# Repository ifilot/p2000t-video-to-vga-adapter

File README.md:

# P2000T video-to-VGA adapter

Hardware and firmware for converting the Philips P2000T RGBS output to
640×480 VGA using a Raspberry Pi Pico or Pico 2.

## Downloads

- [Latest Pico firmware](https://github.com/ifilot/p2000t-video-to-vga-adapter/releases/latest/download/p2000t-vid2vga-pico.uf2)
- [Latest Pico 2 firmware](https://github.com/ifilot/p2000t-video-to-vga-adapter/releases/latest/download/p2000t-vid2vga-pico2.uf2)
- [SAA5050 screen-test cartridge](https://github.com/ifilot/p2000t-video-to-vga-adapter/releases/latest/download/p2000t-screentest.bin)
- [Latest Windows capture viewer installer](https://github.com/ifilot/p2000t-video-to-vga-adapter/releases/latest/download/p2000t-vid2vga-capture-windows-setup.exe)
- [Latest portable Windows capture viewer](https://github.com/ifilot/p2000t-video-to-vga-adapter/releases/latest/download/p2000t-vid2vga-capture-windows.zip)

## Features

- 480×240 RGBs capture using PIO and DMA
- Triple-buffered, frame-boundary VGA updates
- Horizontally qualified CSYNC capture
- 640×480 at 60 Hz RGB444 VGA output
- Three selectable on-screen signal-loss designs
- On-board LED breathing while seeking and blinking during valid capture
- USB serial controls and capture statistics
- Pico 2 USB screen streaming at a target 25 FPS with a Qt 6 viewer
- Selectable raw, legacy guarded, sharp guarded, and Pico 2 three-sample
  126 MHz window reconstruction modes for studying transition instability
- CRC-protected persistence for every Pico 2 reconstruction mode

## Building

Install the Arm GNU toolchain, CMake, and Ninja. On Ubuntu or Debian, install
the required build packages with:

```sh
sudo apt update
sudo apt install cmake ninja-build gcc-arm-none-eabi \
  libnewlib-arm-none-eabi libstdc++-arm-none-eabi-newlib git python3
```

Configure and build the Pico firmware:

```sh
cmake -S . -B build -G Ninja -DCMAKE_BUILD_TYPE=Release -DPICO_BOARD=pico
cmake --build build --parallel
```

For Pico 2, use a separate build directory:

```sh
cmake -S . -B cmake-build-pico2 -G Ninja \
  -DCMAKE_BUILD_TYPE=Release -DPICO_BOARD=pico2
cmake --build cmake-build-pico2 --parallel
```

## USB controls

Connect to the Pico USB serial port and press `h` for help. Useful commands are
`s` for status, `[`/`]` for vertical position, `,`/`.` for sample phase, and
`;`/`'` for the odd-line phase correction. Use `{`/`}` to make the complete
captured line narrower or wider and `w` to reset that rate trim. `<`/`>` moves
the horizontal start, `d` toggles raw/guarded-second-tap reconstruction,
while `1`, `2`, or `3` selects the no-connection artwork.
Each phase tick is nominally 7.94 ns. Each rate step changes the PIO divider by
1/256 and moves the right edge by approximately 0.94 captured pixel while
leaving the sync-anchored left edge in place. Positive odd-line phase samples
odd physical source lines later; positive rate trim widens every line. Pico 2
v0.4.1 Pico 2 factory defaults use line-sliced `window-late` reconstruction
with phase `0`, odd-line correction `+1`, and rate trim `0`. The tuple was
validated against the complete animated teletext test page, including its
blue/white mosaic boundaries and both text polarities. The original Pico
retains raw reconstruction with phase-zero defaults.

Raw reconstruction exposes both 12 MHz samples in every nominal 6 MHz
SAA5050 source dot. Guarded-second-tap reconstruction uses the later sample
for both corresponding VGA pixels unless it matches neither the first tap nor
the following dot's first tap; that isolated intermediate color is replaced
by the current dot's first tap. Pico 2 window reconstruction captures a complete
high-resolution frame and decodes one source line per main-loop service slice;
this retained physical VGA output during live USB validation. It is enabled by
default on Pico 2 and can be omitted from a specialized build with
`-DP2000T_WINDOW_CAPTURE_ENABLED=OFF`. Existing explicitly saved settings remain
authoritative until the user invokes factory reset. Existing v0.3.x records are
migrated when next saved.

For a measured source period near 20092 us, start with rate trim `+2`. The
left-edge compensation allows the existing sample phase to remain unchanged;
compare both edges and also try `+1` because one divider step is necessarily
coarser than the calculated ideal correction.

On Pico 2, `c` starts the recommended continuous PackBits screen stream and
`r` starts an uncompressed stream. Press `q` or Escape to stop binary mode and
return to the console. The alignment and artwork commands remain available
silently while a binary stream is active, allowing the desktop viewer to
configure the adapter without interrupting capture. Stream protocol v4 adds a
64-bit Pico monotonic capture-completion timestamp to every record; the v0.4.1
viewer also accepts legacy v3 records. Factory reset restores and immediately
persists the known-good tuple, palette, and artwork in one USB operation.

> [!NOTE] 
> Screen streaming is intentionally excluded from the Pico/RP2040 build
> for now so its limited SRAM and established VGA timing remain unchanged.

## Pico 2 desktop capture viewer

The Windows viewer shows the P2000T screen live over USB and can save snapshots
as PNG files. It connects to the first detected Pico 2 automatically. When no
P2000T signal is present, it displays the same selected no-connection screen as
the VGA output.

Use **Adapter > Configure Pico 2** to adjust alignment, the independent
odd-line phase correction, and the horizontal sampling-rate trim; choose the
two-tap or 126 MHz window reconstruction; choose the no-connection artwork;
and tune all eight colors. Changes take effect
immediately, which makes calibration easy.
Settings can be restored, reset to their defaults, or saved to the Pico 2 for
the next power-on.

For capture-quality investigation, **Adapter > Record high-resolution
diagnostics** saves a full-frame 63 MHz CSYNC trace and repeated, sync-triggered
126 MHz raw RGBS bursts without reconstruction or palette conversion. See the
[diagnostic recording and analysis guide](docs/diagnostics.md).

For intermittent edge artifacts, **Adapter > Capture calibration sweep**
automatically tests an inclusive sample-phase x horizontal-rate range against
a static source screen. It waits a configurable number of frames after every
acknowledged change, saves multiple consecutive PNGs per setting, and records
the setting and source-frame sequence in a CSV manifest inside a timestamped
analysis directory. The odd-line correction remains fixed at its current
value, and the original live settings are restored after completion or
cancellation.

For unattended optimization, display the supplied SAA5050 screen-test
cartridge and choose **Adapter > Run engineering-screen autotune**. The viewer
forces sharp raw reconstruction, evaluates every phase/rate-trim pair, then
tunes the physical odd lines independently and validates the winner over a
longer run. It applies the result live without writing flash. Every retained
frame, modal candidate image, odd/even instability measurement, one-dot color
transient count, and selection decision is written to a timestamped analysis
directory. See the [engineering autotune guide](docs/engineering-autotune.md).

For AI-directed investigation, the invisible **Codex lab agent** owns the
Windows Pico connection without opening the viewer. Codex can query live state,
apply non-persistent sampling settings, explicitly persist a chosen tuple,
request settled multi-frame captures, receive modal/instability
metrics, inspect the PNGs, and adapt the next experiment without a person
operating a GUI. The Windows agent and WSL client exchange
atomic JSON files through `D:\tmp\p2000t-codex-lab`; see the
[Codex lab guide](docs/codex-lab.md).
The [windowed reconstruction design](docs/windowed-reconstruction.md) explains
the six-tap PIO path and its per-frame evidence counters.

Download either the installer or portable ZIP from [Downloads](#downloads).
The installer adds the viewer to the Start menu and includes an uninstaller.

## License

Firmware and viewer sources are
[GPL-3.0-or-later](LICENSES/GPL-3.0-or-later.txt). Hardware design files are
licensed under CERN-OHL-S-2.0; see [pcb/LICENSE.md](pcb/LICENSE.md).

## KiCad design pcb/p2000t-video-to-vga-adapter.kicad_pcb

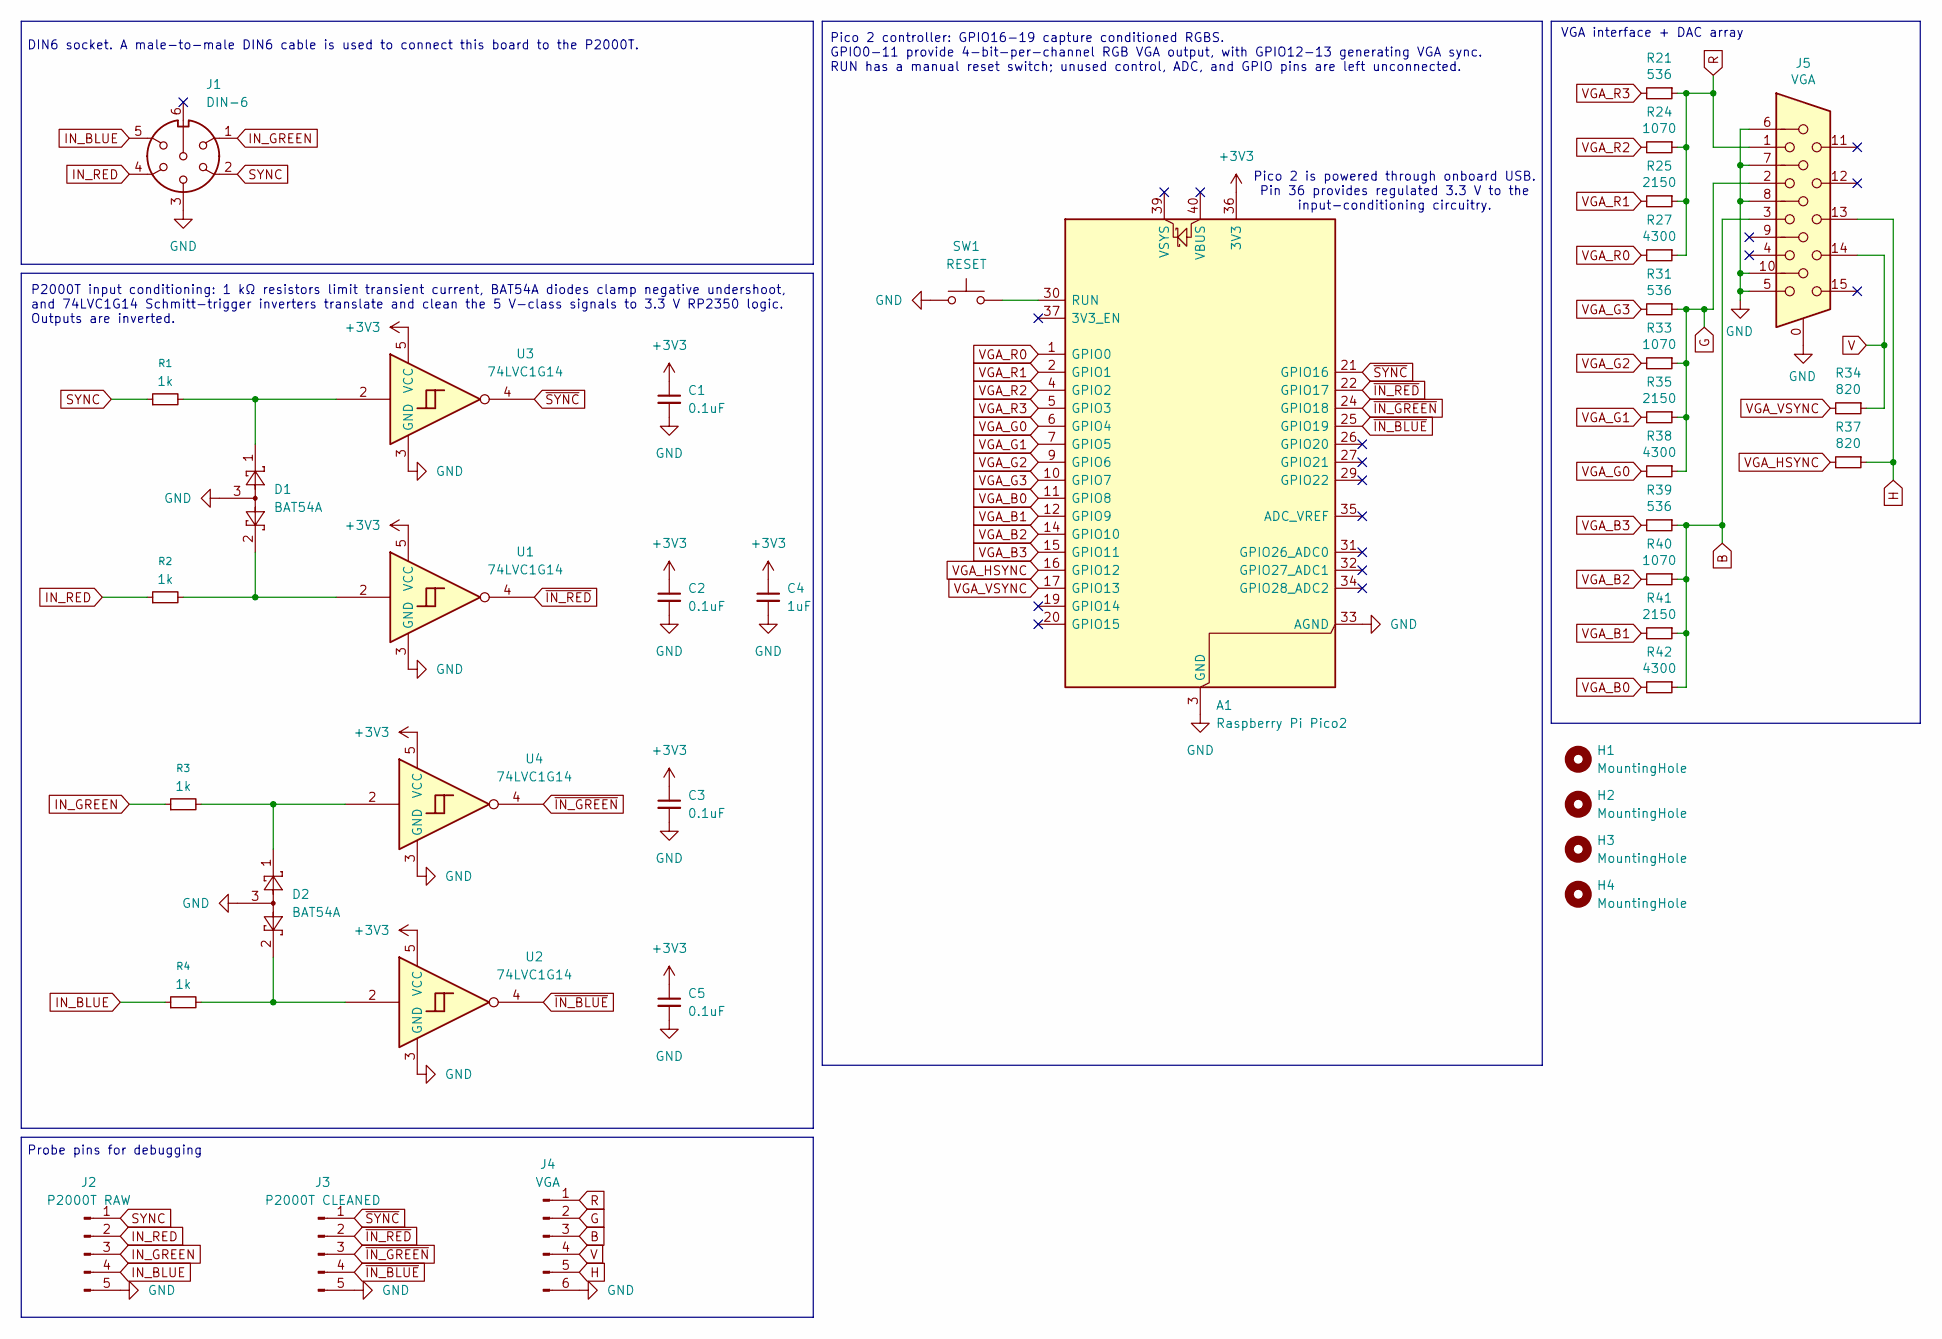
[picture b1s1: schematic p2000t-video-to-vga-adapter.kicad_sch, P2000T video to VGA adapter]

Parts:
A1: Raspberry Pi Pico2; RaspberryPi_Pico_Common_Unspecified
C1, C2, C3, C5: 0.1uF; C_0805_2012Metric_Pad1.18x1.45mm_HandSolder; LCSC Part # C28233
C4: 1uF; C_0805_2012Metric_Pad1.18x1.45mm_HandSolder; LCSC Part # C28323
D1, D2: BAT54A; SOT-23; LCSC Part # C130910
H1, H2, H3, H4: MountingHole; MountingHole_3.2mm_M3_Pad_Via
J1: DIN-6; SDF-60J
J2: P2000T RAW; PinHeader_1x05_P2.54mm_Vertical
J3: P2000T CLEANED; PinHeader_1x05_P2.54mm_Vertical
J4: VGA; PinHeader_1x06_P2.54mm_Vertical
J5: VGA
R1, R2, R3, R4: 1k; R_0805_2012Metric_Pad1.20x1.40mm_HandSolder; LCSC Part # C17513
R21, R31, R39: 536; R_0805_2012Metric_Pad1.20x1.40mm_HandSolder; LCSC Part # C343952
R24, R33, R40: 1070; R_0805_2012Metric_Pad1.20x1.40mm_HandSolder; LCSC Part # C865249
R25, R35, R41: 2150; R_0805_2012Metric_Pad1.20x1.40mm_HandSolder; LCSC Part # C515726
R27, R38, R42: 4300; R_0805_2012Metric_Pad1.20x1.40mm_HandSolder; LCSC Part # C473294
R34, R37: 820; R_0805_2012Metric_Pad1.20x1.40mm_HandSolder; LCSC Part # C865664
SW1: RESET; SW_PUSH_6mm
U1, U2, U3, U4: 74LVC1G14; SOT-23-5_HandSoldering; LCSC Part # C131093

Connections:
+3V3: A1.36 (3V3), C1.1, C2.1, C3.1, C4.1, C5.1, U1.5 (VCC), U2.5 (VCC), U3.5 (VCC), U4.5 (VCC)
B: J4.3, J5.3, R39.1, R40.1, R41.1, R42.1
G: J4.2, J5.2, R31.1, R33.1, R35.1, R38.1
GND: A1.3 (GND), A1.8 (GND), A1.13 (GND), A1.18 (GND), A1.23 (GND), A1.28 (GND), A1.33 (AGND), A1.38 (GND), C1.2, C2.2, C3.2, C4.2, C5.2, D1.3, D2.3, J1.3, J2.5, J3.5, J4.6, J5.0, J5.5, J5.6, J5.7, J5.8, J5.10, SW1.1, U1.3 (GND), U2.3 (GND), U3.3 (GND), U4.3 (GND)
H: J4.5, J5.13, R37.1
IN_BLUE: J1.5, J2.4, R4.1
IN_GREEN: J1.1, J2.3, R3.1
IN_RED: J1.4, J2.2, R2.1
unnamed: A1.30 (RUN), SW1.2
unnamed: D1.1, R1.2, U3.2
unnamed: D1.2, R2.2, U1.2
unnamed: D2.1, R3.2, U4.2
unnamed: D2.2, R4.2, U2.2
R: J4.1, J5.1, R21.1, R24.1, R25.1, R27.1
SYNC: J1.2, J2.1, R1.1
V: J4.4, J5.14, R34.1
VGA_B0: A1.11 (GPIO8), R42.2
VGA_B1: A1.12 (GPIO9), R41.2
VGA_B2: A1.14 (GPIO10), R40.2
VGA_B3: A1.15 (GPIO11), R39.2
VGA_G0: A1.6 (GPIO4), R38.2
VGA_G1: A1.7 (GPIO5), R35.2
VGA_G2: A1.9 (GPIO6), R33.2
VGA_G3: A1.10 (GPIO7), R31.2
VGA_HSYNC: A1.16 (GPIO12), R37.2
VGA_R0: A1.1 (GPIO0), R27.2
VGA_R1: A1.2 (GPIO1), R25.2
VGA_R2: A1.4 (GPIO2), R24.2
VGA_R3: A1.5 (GPIO3), R21.2
VGA_VSYNC: A1.17 (GPIO13), R34.2
~IN_BLUE: A1.25 (GPIO19), J3.4, U2.4
~IN_GREEN: A1.24 (GPIO18), J3.3, U4.4
~IN_RED: A1.22 (GPIO17), J3.2, U1.4
~SYNC: A1.21 (GPIO16), J3.1, U3.4

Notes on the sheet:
VGA interface + DAC array
DIN6 socket. A male-to-male DIN6 cable is used to connect this board to the P2000T.
P2000T input conditioning: 1 kΩ resistors limit transient current, BAT54A diodes clamp negative undershoot, and 74LVC1G14 Schmitt-trigger inverters translate and clean the 5 V-class signals to 3.3 V RP2350 logic. Outputs are inverted.
Pico 2 controller: GPIO16-19 capture conditioned RGBS. GPIO0-11 provide 4-bit-per-channel RGB VGA output, with GPIO12-13 generating VGA sync. RUN has a manual reset switch; unused control, ADC, and GPIO pins are left unconnected.
Pico 2 is powered through onboard USB. Pin 36 provides regulated 3.3 V to the input-conditioning circuitry.
Probe pins for debugging

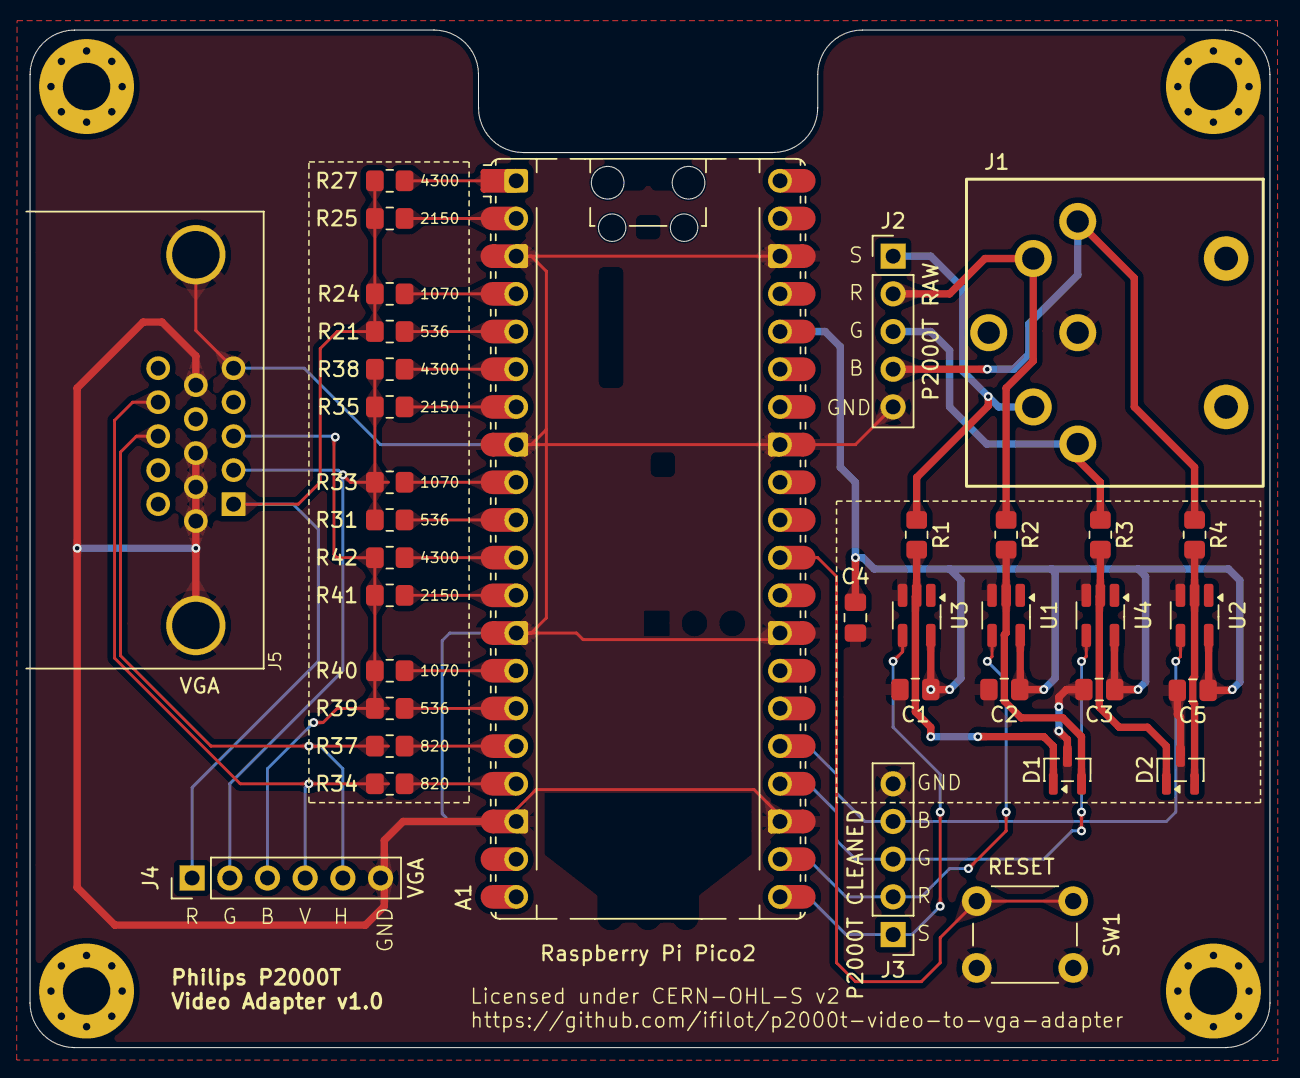
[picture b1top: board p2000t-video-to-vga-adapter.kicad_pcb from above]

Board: 2 copper layers, 83.6 x 68.6 mm, 40 parts (0 on the bottom side), 34 nets.

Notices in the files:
README.md:
License: GPL-3.0-or-later / CERN-OHL-S-2.0
pcb/p2000t-video-to-vga-adapter.kicad_pcb:
Licensed under CERN-OHL-S v2
